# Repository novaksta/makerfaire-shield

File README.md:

# Game console shield for NUCLEO-F412ZG

It is intended for [MakeCode Arcade](https://arcade.makecode.com/) as F4 target (see available material on (https://arcade.makecode.com/hardware/adding) if you wish to customize),

with additional [lcd module](https://www.laskakit.cz/128x160-barevny-lcd-tft-displej-1-8--spi/)

Available are [bootloader firmware binaries](bootloaders/v2-st7735/bootloader.bin)

There is available kicad project for the board in [pcb foler](pcb) (including [gerbers with BOM](pcb/jlcpcb/production_files/production_files-min.7z) in jlcpcb-friendly format).

There are available [workshop slides](slajdy.pdf) for Maker Faire in Prague 2026 (in czech language) that describes "getting started" process. 

There are also available workshop materials for Maker Faire in Brno 2025 where used NUCLEO-F411RE/NUCLEO-F401RE -- please see releases section.

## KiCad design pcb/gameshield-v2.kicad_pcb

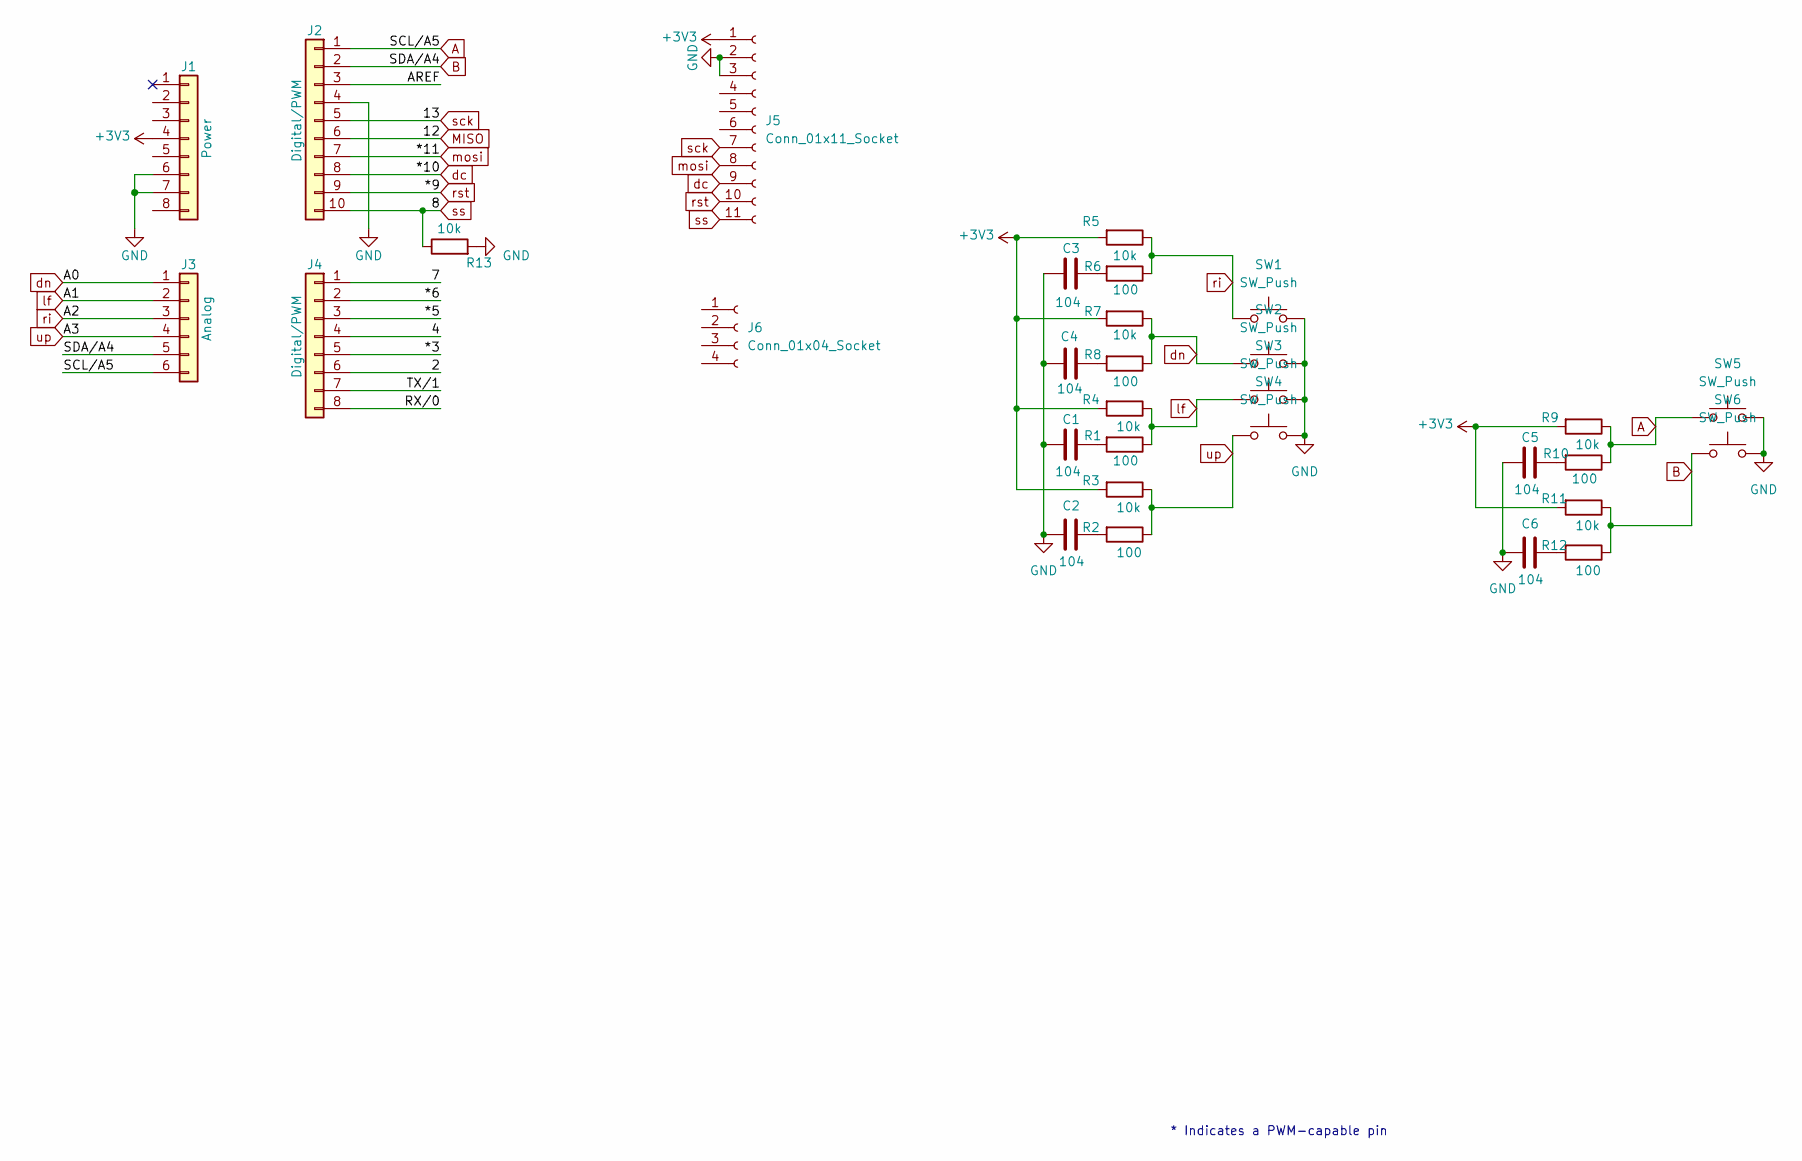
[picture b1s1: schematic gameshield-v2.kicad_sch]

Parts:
C1, C2, C3, C4, C5, C6: 104; C_0805_2012Metric_Pad1.18x1.45mm_HandSolder
J1: Power; PinHeader_1x08_P2.54mm_Vertical
J2: Digital/PWM; PinHeader_1x10_P2.54mm_Vertical
J3: Analog; PinHeader_1x06_P2.54mm_Vertical
J4: Digital/PWM; PinHeader_1x08_P2.54mm_Vertical
J5: Conn_01x11_Socket; PinHeader_1x11_P2.54mm_Vertical
J6: Conn_01x04_Socket; PinHeader_1x04_P2.54mm_Vertical
R1, R2, R6, R8, R10, R12: 100; R_0805_2012Metric_Pad1.20x1.40mm_HandSolder
R3, R4, R5, R7, R9, R11, R13: 10k; R_0805_2012Metric_Pad1.20x1.40mm_HandSolder
SW1, SW2, SW3, SW4, SW5, SW6: SW_Push; SW_Push_1P1T_XKB_TS-1187A

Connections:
+3V3: J1.4, J5.1, R3.2, R4.2, R5.2, R7.2, R9.2, R11.2
/2: J4.6
/4: J4.4
/7: J4.1
/*3: J4.5
/*5: J4.3
/*6: J4.2
/AREF: J2.3
/RX/0: J4.8
/TX/1: J4.7
A: J2.1, J3.6, R9.1, R10.1, SW5.1
B: J2.2, J3.5, R11.1, R12.1, SW6.1
GND: C1.2, C2.2, C3.2, C4.2, C5.2, C6.2, J1.6, J1.7, J2.4, J5.2, J5.3, R13.2, SW1.2, SW2.2, SW3.2, SW4.2, SW5.2, SW6.2
MISO: J2.6
unnamed: C1.1, R1.2
unnamed: C2.1, R2.2
unnamed: C3.1, R6.2
unnamed: C4.1, R8.2
unnamed: C5.1, R10.2
unnamed: C6.1, R12.2
dc: J2.8, J5.9
dn: J3.1, R7.1, R8.1, SW2.1
lf: J3.2, R1.1, R4.1, SW3.1
mosi: J2.7, J5.8
ri: J3.3, R5.1, R6.1, SW1.1
rst: J2.9, J5.10
sck: J2.5, J5.7
ss: J2.10, J5.11, R13.1
up: J3.4, R2.1, R3.1, SW4.1

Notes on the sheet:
* Indicates a PWM-capable pin

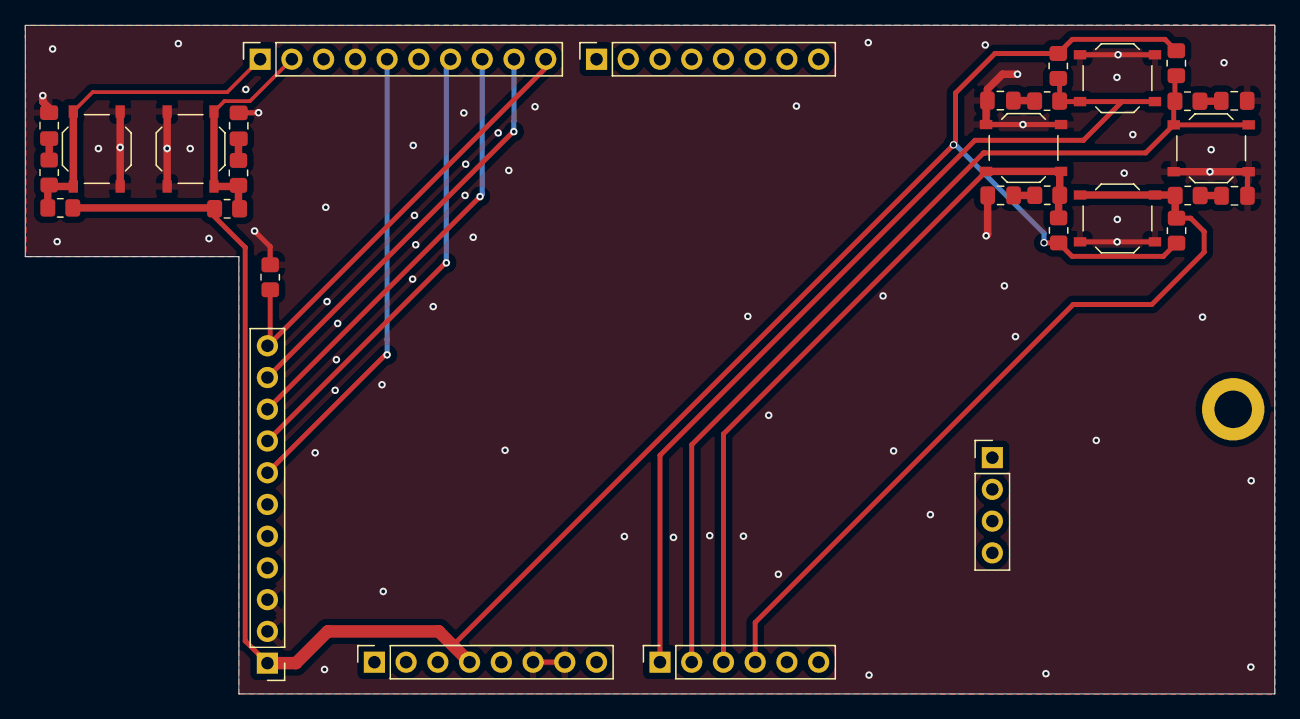
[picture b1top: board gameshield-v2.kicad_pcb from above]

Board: 2 copper layers, 100.0 x 53.5 mm, 31 parts (0 on the bottom side), 19 nets.

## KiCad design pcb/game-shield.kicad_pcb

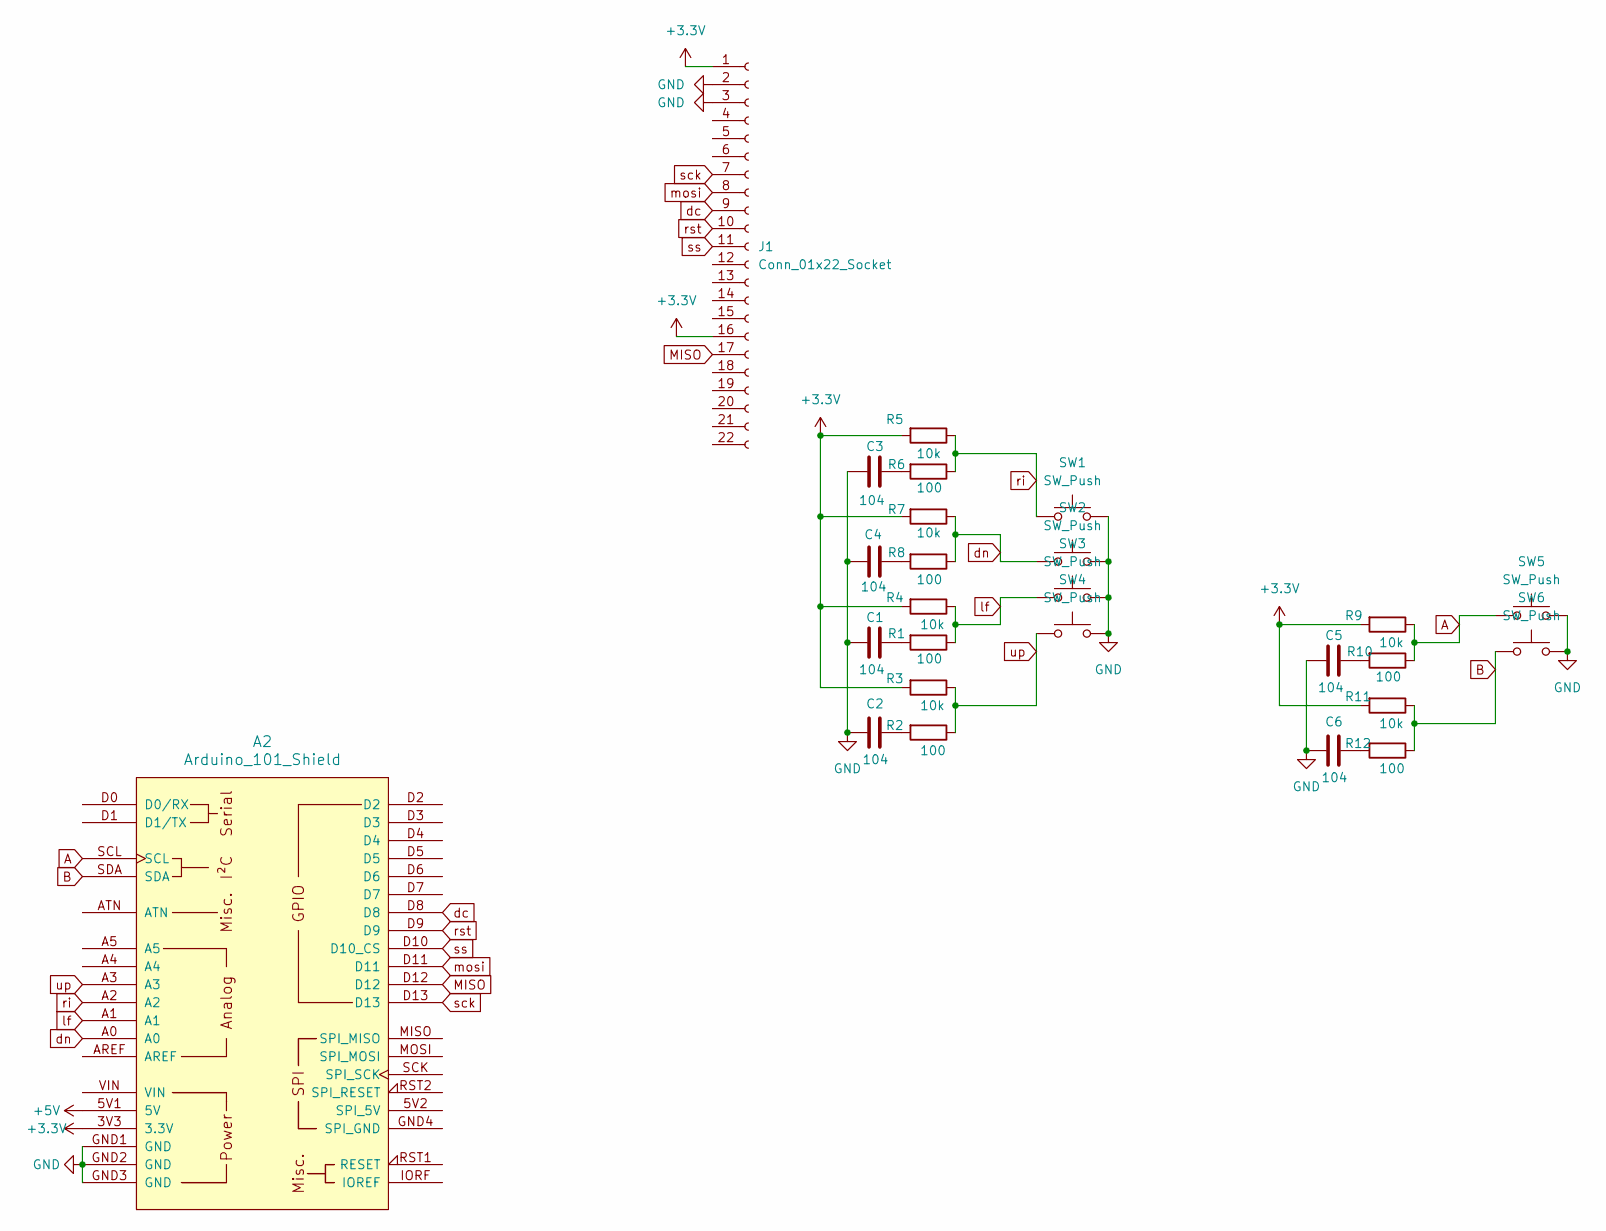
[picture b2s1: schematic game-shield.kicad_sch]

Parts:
A2: Arduino_101_Shield
C1, C2, C3, C4, C5, C6: 104; C_1206_3216Metric_Pad1.33x1.80mm_HandSolder
J1: Conn_01x22_Socket; lcd-st7735-cheap
R1, R2, R6, R8, R10, R12: 100; R_1206_3216Metric_Pad1.30x1.75mm_HandSolder
R3, R4, R5, R7, R9, R11: 10k; R_1206_3216Metric_Pad1.30x1.75mm_HandSolder
SW1, SW2, SW3, SW4, SW5, SW6: SW_Push; SW_PUSH_6mm

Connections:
+3.3V: A2.3V3 (3.3V), J1.1, J1.16, R3.2, R4.2, R5.2, R7.2, R9.2, R11.2
+5V: A2.5V1 (5V)
A: A2.SCL, R9.1, R10.1, SW5.1
B: A2.SDA, R11.1, R12.1, SW6.1
GND: A2.GND1 (GND), A2.GND2 (GND), A2.GND3 (GND), C1.2, C2.2, C3.2, C4.2, C5.2, C6.2, J1.2, J1.3, SW1.2, SW2.2, SW3.2, SW4.2, SW5.2, SW6.2
MISO: A2.D12, J1.17
unnamed: C1.1, R1.2
unnamed: C2.1, R2.2
unnamed: C3.1, R6.2
unnamed: C4.1, R8.2
unnamed: C5.1, R10.2
unnamed: C6.1, R12.2
dc: A2.D8, J1.9
dn: A2.A0, R7.1, R8.1, SW2.1
lf: A2.A1, R1.1, R4.1, SW3.1
mosi: A2.D11, J1.8
ri: A2.A2, R5.1, R6.1, SW1.1
rst: A2.D9, J1.10
sck: A2.D13, J1.7
ss: A2.D10 (D10_CS), J1.11
up: A2.A3, R2.1, R3.1, SW4.1

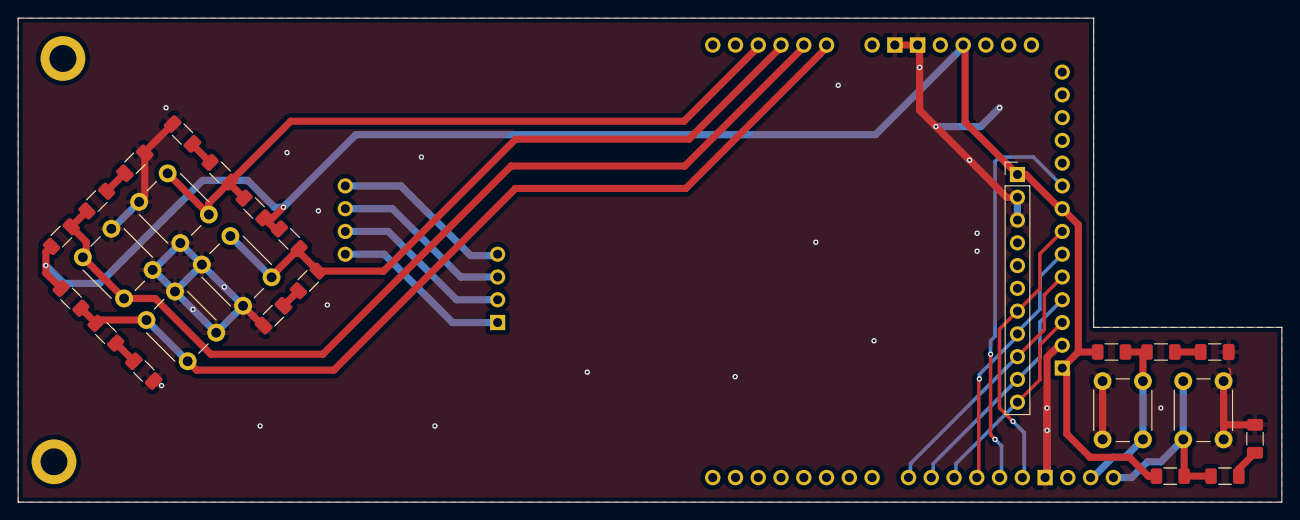
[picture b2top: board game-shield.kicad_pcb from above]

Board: 2 copper layers, 141.0 x 54.0 mm, 26 parts (0 on the bottom side), 20 nets.

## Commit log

2026-04-27 f412
2026-04-27 clean
2026-04-27 readme
2026-04-28 pcb upload
